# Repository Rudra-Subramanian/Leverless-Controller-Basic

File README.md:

# Leverless-Controller-Basic
Cheap(?) leverless controller design

# Credits

- 3d models from Flatbox https://github.com/jfedor2/flatbox - altered to fit case
- generated models with turbocase https://turbocase.org/

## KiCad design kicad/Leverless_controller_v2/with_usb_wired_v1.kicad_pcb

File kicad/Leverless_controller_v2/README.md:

# Second version of pcb with USB

## Changes

slimmer

changing mounting hole position

adding user.6 and user.7 for turbocase

gateron hotswap sockets for gateron ks-33

## Specs

3.5 mm mounting holes

### credits

key switch footprint : https://github.com/siderakb/key-switches.pretty/tree/main

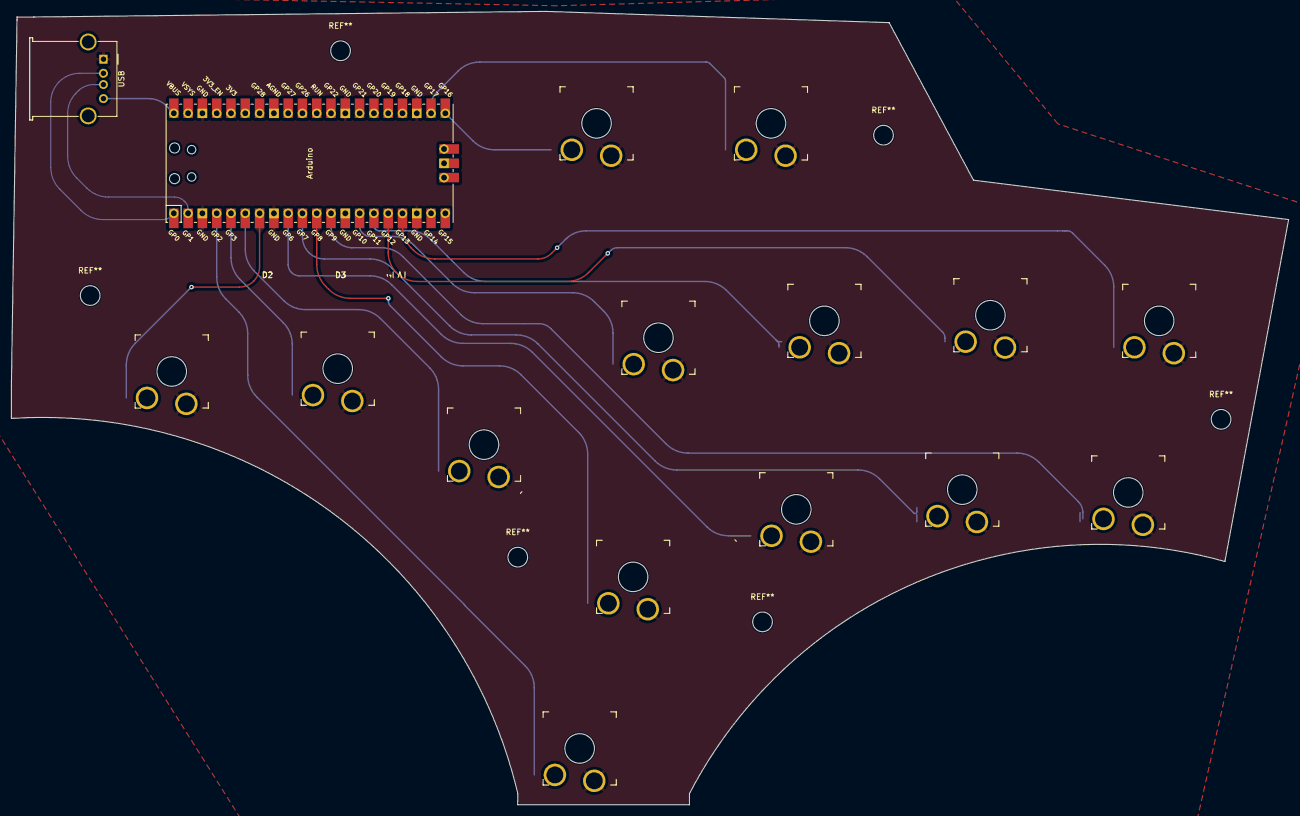
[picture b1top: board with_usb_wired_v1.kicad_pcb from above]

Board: 2 copper layers, 227.0 x 141.0 mm, 16 parts (0 on the bottom side), 18 nets.

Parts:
Arduino: RPi_Pico_SMD_TH
S1, S2, S3, S4, S5, S6, S7, S8, S9, S10, S11, S12, S13, S14: SW_Gateron_LowProfile_HotSwap_PTH_footprint
USB: USB_A_Molex_67643_Horizontal

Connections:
D+: Arduino.1, USB.2
D-: Arduino.2, USB.3
GND: Arduino.3, Arduino.8, Arduino.18, Arduino.23, Arduino.28, Arduino.38, S1.2, S2.2, S3.2, S4.2, S5.2, S6.2, S7.2, S8.2, S9.2, S10.2, S11.2, S12.2, S13.2, S14.2, USB.1
VCC: Arduino.40, USB.4
down: Arduino.5, S2.1
k0: Arduino.11, S5.1
k1: Arduino.9, S7.1
k2: Arduino.10, S9.1
k3: Arduino.12, S11.1
left: Arduino.7, S1.1
p0: Arduino.14, S6.1
p1: Arduino.15, S8.1
p2: Arduino.16, S10.1
p3: Arduino.17, S12.1
right: Arduino.6, S3.1
select: Arduino.22, S14.1
start: Arduino.21, S13.1
up: Arduino.4, S4.1

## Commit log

2025-05-28 adding kicad files
2025-05-29 editing kicad
2025-06-03 editing kicad file
2025-06-03 adding output gerberfile
2025-06-06 editing pcb
